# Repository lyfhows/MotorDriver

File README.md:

A custom KiCad board built around the L298N (kept deliberately, not replaced by a MOSFET bridge). It improves on the standard red module with Schottky 
flyback diodes, input protection, a proper onboard logic supply, voltage, current and power monitoring over I2C, and a hardware overcurrent limit that 
works without firmware.

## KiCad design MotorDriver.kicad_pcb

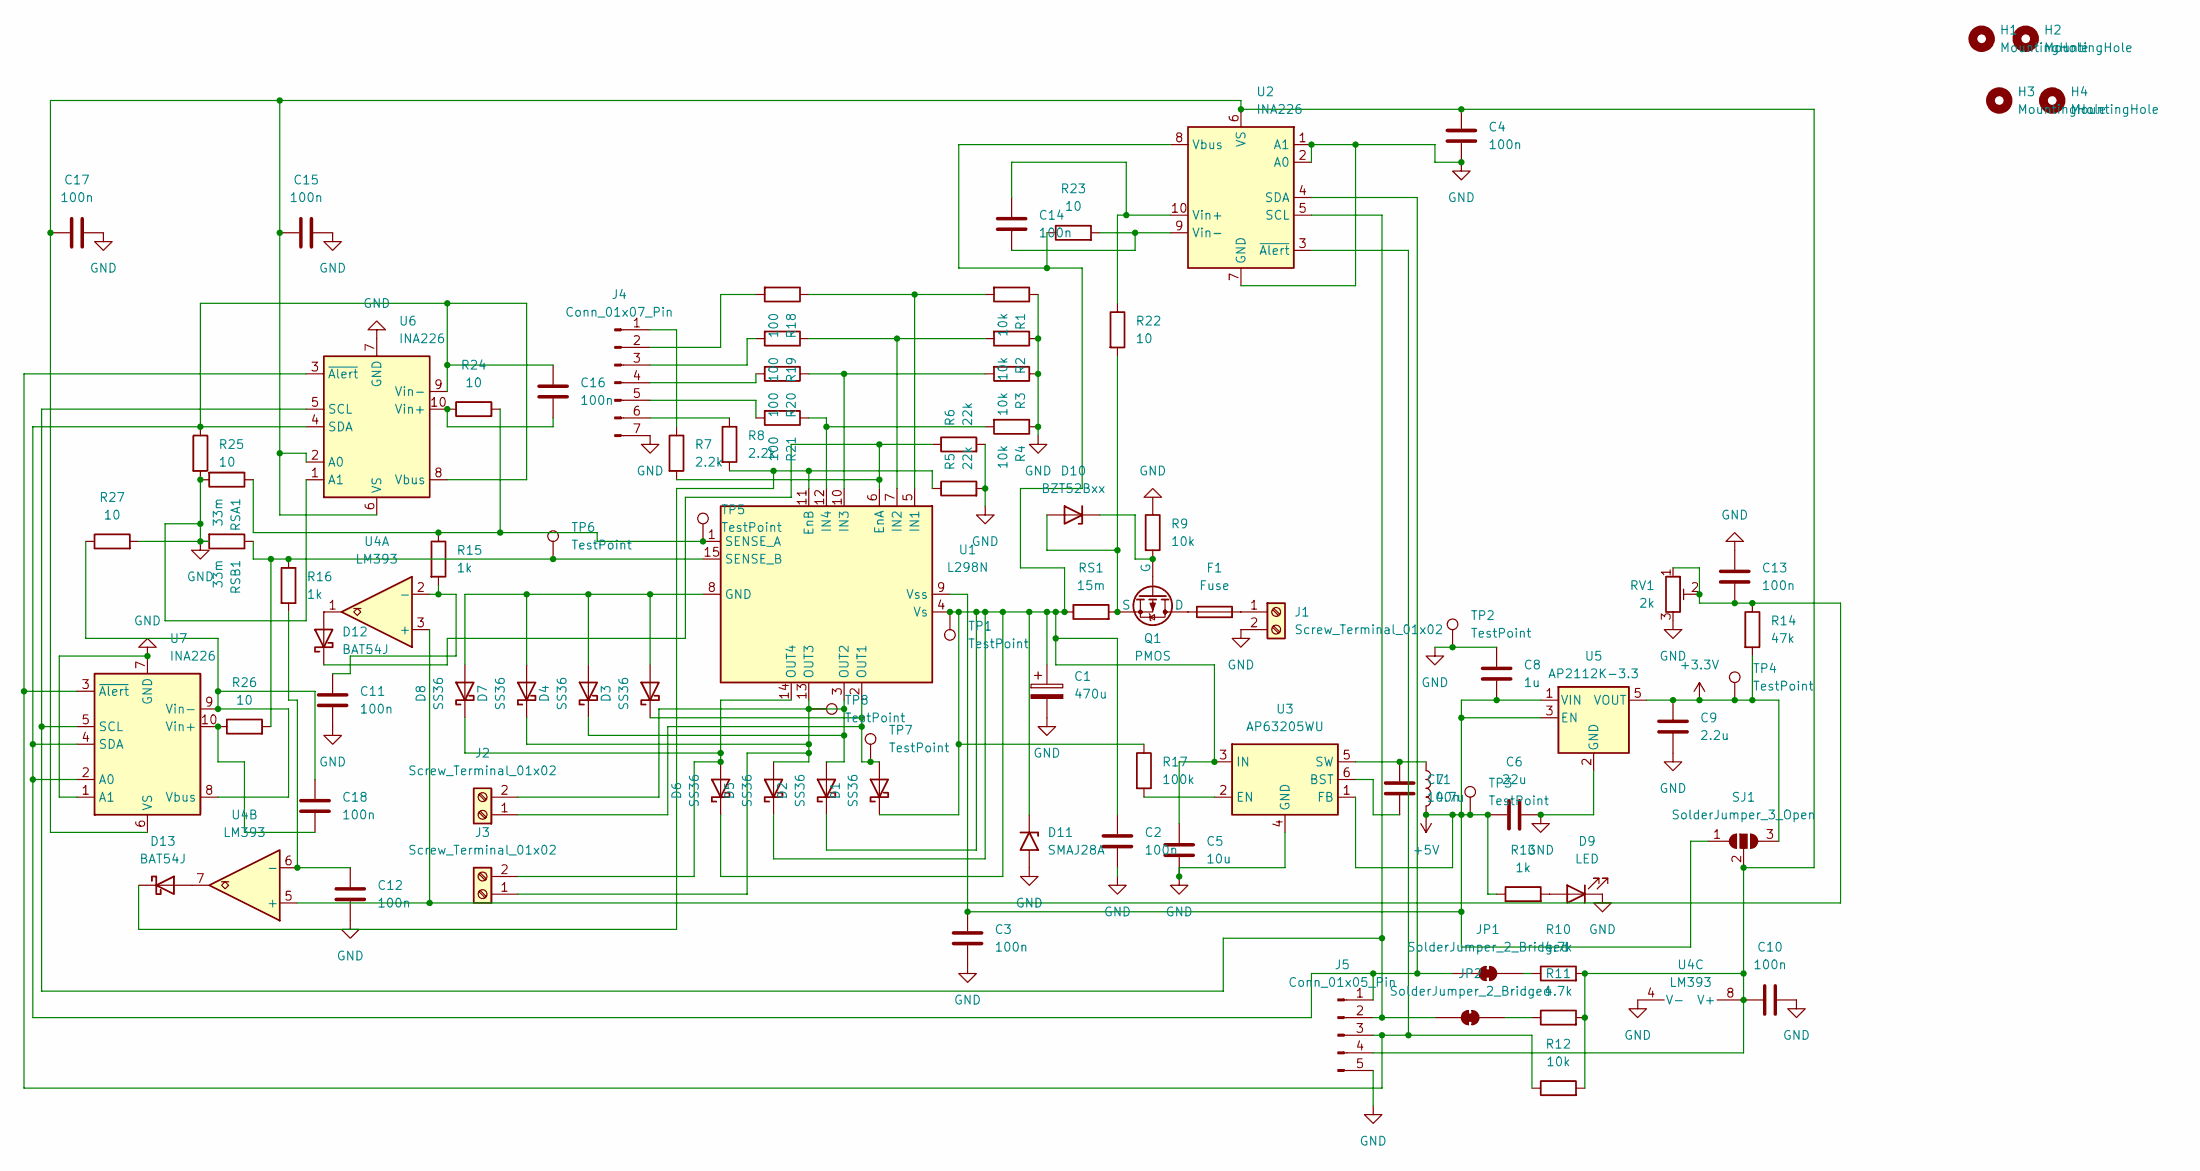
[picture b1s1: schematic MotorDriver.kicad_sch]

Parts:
C1: 470u; CP_Radial_D10.0mm_P5.00mm_P7.50mm
C2, C3, C4, C7, C10, C11, C12, C13, C14, C15, C16, C17, C18: 100n; C_0805_2012Metric_Pad1.18x1.45mm_HandSolder
C5: 10u; C_1206_3216Metric_Pad1.33x1.80mm_HandSolder
C6: 22u; C_1206_3216Metric_Pad1.33x1.80mm_HandSolder
C8: 1u; C_0805_2012Metric_Pad1.18x1.45mm_HandSolder
C9: 2.2u; C_0805_2012Metric_Pad1.18x1.45mm_HandSolder
D1, D2, D3, D4, D5, D6, D7, D8: SS36; D_SMA
D9: LED; LED_0805_2012Metric_Pad1.15x1.40mm_HandSolder
D10: BZT52Bxx; D_SOD-123F
D11: SMAJ28A; D_SMA
D12, D13: BAT54J; D_SOD-323F
F1: Fuse; Fuseholder_Cylinder-5x20mm_Schurter_0031_8201_Horizontal_Op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
H1, H2, H3, H4: MountingHole; MountingHole_3.2mm_M3
J1, J2, J3: Screw_Terminal_01x02; TerminalBlock_Phoenix_MKDS-1,5-2-5.08_1x02_P5.08mm_Horizont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
J4: Conn_01x07_Pin; PinHeader_1x07_P2.54mm_Vertical
J5: Conn_01x05_Pin; PinHeader_1x05_P2.54mm_Vertical
JP1, JP2: SolderJumper_2_Bridged; SolderJumper-2_P1.3mm_Bridged_RoundedPad1.0x1.5mm
L1: 4.7u; L_Bourns_SRN6045TA
Q1: PMOS; TO-252-2
R1, R2, R3, R4, R9, R12: 10k; R_0603_1608Metric_Pad0.98x0.95mm_HandSolder
R5, R6: 22k; R_0603_1608Metric_Pad0.98x0.95mm_HandSolder
R7, R8: 2.2k; R_0603_1608Metric_Pad0.98x0.95mm_HandSolder
R10, R11: 4.7k; R_0603_1608Metric_Pad0.98x0.95mm_HandSolder
R13, R15, R16: 1k; R_0603_1608Metric_Pad0.98x0.95mm_HandSolder
R14: 47k; R_0603_1608Metric_Pad0.98x0.95mm_HandSolder
R17: 100k; R_0603_1608Metric_Pad0.98x0.95mm_HandSolder
R18, R19, R20, R21: 100; R_0603_1608Metric_Pad0.98x0.95mm_HandSolder
R22, R23, R24, R25, R26, R27: 10; R_0603_1608Metric_Pad0.98x0.95mm_HandSolder
RS1: 15m; R_2512_6332Metric_Pad1.40x3.35mm_HandSolder
RSA1: 33m; R_2512_6332Metric_Pad1.40x3.35mm_HandSolder
RSB1: 33m; R_2512_6332Metric_Pad1.40x3.35mm_HandSolder
RV1: 2k; Potentiometer_Bourns_3296W_Vertical
SJ1: SolderJumper_3_Open; SolderJumper-3_P1.3mm_Open_RoundedPad1.0x1.5mm
TP1, TP2, TP3, TP4, TP5, TP6, TP7, TP8: TestPoint; TestPoint_Pad_D1.5mm
U1: L298N; TO-220-15_P2.54x5.08mm_StaggerOdd_Lead4.58mm_Vertical
U2, U6, U7: INA226; TSSOP-10_3x3mm_P0.5mm
U3: AP63205WU; TSOT-23-6
U4: LM393; SOIC-8_3.9x4.9mm_P1.27mm
U5: AP2112K-3.3; SOT-23-5

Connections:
+3.3V: C9.1, R14.2, SJ1.3 (B), TP4.1 (1_1), U5.5 (VOUT)
+5V: C3.1, C6.1, C8.2, L1.2, R13.1, SJ1.1 (A), TP3.1 (1_1), U1.9 (Vss), U3.1 (FB), U5.1 (VIN), U5.3 (EN)
GND: C1.2, C2.2, C3.2, C4.2, C5.2, C6.2, C8.1, C9.2, C10.2, C11.2, C12.2, C13.1, C15.2, C17.2, D9.1 (K), D11.2 (A2), J1.2, J4.7, J5.5, R1.1, R2.1, R3.1, R4.1, R5.2, R6.2, R9.1, R25.2, R27.2, RSA1.2, RSB1.2, RV1.3, TP2.1 (1_1), U2.1 (A1), U2.2 (A0), U2.7 (GND), U3.4 (GND), U4.4 (V-), U5.2 (GND), U6.1 (A1), U6.7 (GND), U7.1 (A1), U7.7 (GND)
unnamed: D1.2 (A), D3.1 (K), J2.1, TP7.1 (1_1), U1.2 (OUT1)
unnamed: C1.1, C2.1, C5.1, D1.1 (K), D2.1 (K), D5.1 (K), D6.1 (K), D11.1 (A1), R17.1, R23.1, RS1.1, TP1.1 (1_1), U1.4 (Vs), U2.8 (Vbus), U3.3 (IN)
unnamed: D2.2 (A), D4.1 (K), D5.2 (A), D7.1 (K), J2.2, J3.1, TP8.1 (1_1), U1.3 (OUT2), U1.13 (OUT3)
unnamed: D3.2 (A), D4.2 (A), D7.2 (A), D8.2 (A), U1.8 (GND)
unnamed: D6.2 (A), D8.1 (K), J3.2, U1.14 (OUT4)
unnamed: D9.2 (A), R13.2
unnamed: D10.2 (A), Q1.3 (S), R22.2, RS1.2
unnamed: D10.1 (K), Q1.2 (G), R9.2
unnamed: D12.2 (A), U4.1
unnamed: D12.1 (K), R6.1, R7.2, U1.6 (EnA)
unnamed: D13.2 (A), U4.7
unnamed: D13.1 (K), R5.1, R8.2, U1.11 (EnB)
unnamed: F1.2, J1.1
unnamed: J4.1, R7.1
unnamed: J4.2, R18.2
unnamed: J4.3, R19.2
unnamed: J4.4, R20.2
unnamed: J4.5, R21.2
unnamed: J4.6, R8.1
unnamed: C16.1, J5.1, JP1.1 (A), R25.1, U2.4 (SDA), U6.4 (SDA), U6.8 (Vbus), U6.9 (Vin-), U7.2 (A0), U7.4 (SDA)
unnamed: J5.2, JP2.1 (A), U2.5 (SCL), U6.5 (SCL), U7.5 (SCL)
unnamed: J5.3, R12.1, U2.3 (~Alert), U6.3 (~Alert), U7.3 (~Alert)
unnamed: C4.1, C10.1, C15.1, C17.1, J5.4, R10.2, R11.2, R12.2, SJ1.2 (C), U2.6 (VS), U4.8 (V+), U6.2 (A0), U6.6 (VS), U7.6 (VS)
unnamed: JP1.2 (B), R10.1
unnamed: JP2.2 (B), R11.1
unnamed: F1.1, Q1.1 (D)
unnamed: R1.2, R18.1, U1.5 (IN1)
unnamed: R2.2, R19.1, U1.7 (IN2)
unnamed: R3.2, R20.1, U1.10 (IN3)
unnamed: R4.2, R21.1, U1.12 (IN4)
unnamed: R15.1, R24.2, RSA1.1, TP5.1 (1_1), U1.1 (SENSE_A)
unnamed: R16.1, R26.2, RSB1.1, TP6.1 (1_1), U1.15 (SENSE_B)
unnamed: C14.1, R22.1, U2.10 (Vin+)
unnamed: C14.2, R23.2, U2.9 (Vin-)
unnamed: C7.2, U3.6 (BST)
unnamed: R17.2, U3.2 (EN)
unnamed: C7.1, L1.1, U3.5 (SW)
unnamed: C13.2, R14.1, RV1.1, RV1.2, U4.3 (+), U4.5 (+)
unnamed: C11.1, R15.2, U4.2 (-)
unnamed: C12.1, R16.2, U4.6 (-)
unnamed: C16.2, R24.1, U6.10 (Vin+)
unnamed: C18.1, R27.1, U7.8 (Vbus), U7.9 (Vin-)
unnamed: C18.2, R26.1, U7.10 (Vin+)

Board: 2 copper layers, 92 parts (0 on the bottom side), 46 nets, no tracks yet.

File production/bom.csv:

Designator,Footprint,Quantity,Value,LCSC Part #
C1,CP_Radial_D10.0mm_P5.00mm_P7.50mm,1,470u,
"C10, C11, C12, C13, C14, C15, C16, C17, C18, C2, C3, C4, C7",0805,13,100n,
C5,1206,1,10u,
C6,1206,1,22u,
C8,0805,1,1u,
C9,0805,1,2.2u,
"D1, D2, D3, D4, D5, D6, D7, D8",D_SMA,8,SS36,
D10,D_SOD-123F,1,BZT52Bxx,
D11,D_SMA,1,SMAJ28A,
"D12, D13",D_SOD-323F,2,BAT54J,
D9,0805,1,LED,
F1,Fuseholder_Cylinder-5x20mm_Schurter_0031_8201_Horizontal_Open,1,Fuse,
"J1, J2, J3","TerminalBlock_Phoenix_MKDS-1,5-2-5.08_1x02_P5.08mm_Horizontal",3,Screw_Terminal_01x02,
J4,PinHeader_1x07_P2.54mm_Vertical,1,Conn_01x07_Pin,
J5,PinHeader_1x05_P2.54mm_Vertical,1,Conn_01x05_Pin,
L1,L_Bourns_SRN6045TA,1,4.7u,
Q1,TO-252-2,1,PMOS,
"R1, R12, R2, R3, R4, R9",0603,6,10k,
"R10, R11",0603,2,4.7k,
"R13, R15, R16",0603,3,1k,
R14,0603,1,47k,
R17,0603,1,100k,
"R18, R19, R20, R21",0603,4,100,
"R22, R23, R24, R25, R26, R27",0603,6,10,
"R5, R6",0603,2,22k,
"R7, R8",0603,2,2.2k,
RS1,2512,1,15m,
"RSA1, RSB1",2512,2,33m,
RV1,Potentiometer_Bourns_3296W_Vertical,1,2k,
"TP1, TP2, TP3, TP4, TP5, TP6, TP7, TP8",TestPoint_Pad_D1.5mm,8,TestPoint,
U1,TO-220-15_P2.54x5.08mm_StaggerOdd_Lead4.58mm_Vertical,1,L298N,
"U2, U6, U7",TSSOP-10_3x3mm_P0.5mm,3,INA226,
U3,TSOT-23-6,1,AP63205WU,
U4,SOIC-8_3.9x4.9mm_P1.27mm,1,LM393,
U5,SOT-23-5,1,AP2112K-3.3,
